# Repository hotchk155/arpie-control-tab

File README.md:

# arpie-control-tab

This project is a reference design for the 3 x potentiometer plus one momentary switch sidecar board for the ARPIE arpeggiator

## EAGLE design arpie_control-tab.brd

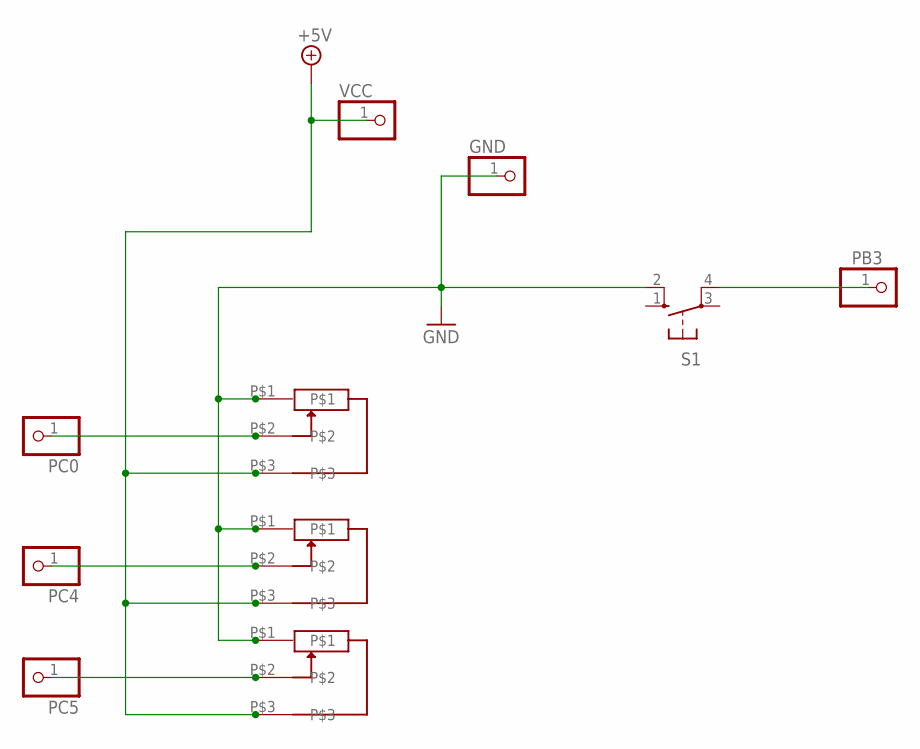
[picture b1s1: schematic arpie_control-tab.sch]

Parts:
GND: PINHD-1X1; 1X01
PB3: PINHD-1X1; 1X01
PC0, PC4, PC5: PINHD-1X1; 1X01
S1: 10-XX; B3F-10XX
U$1, U$2, U$3: PCBMOUNTPOT
VCC: PINHD-1X1; 1X01

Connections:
+5V: U$1.P$3, U$2.P$3, U$3.P$3, VCC.1
GND: GND.1, S1.2 (S1), U$1.P$1, U$2.P$1, U$3.P$1
unnamed: PB3.1, S1.4 (P1)
unnamed: PC0.1, U$1.P$2
unnamed: PC4.1, U$2.P$2
unnamed: PC5.1, U$3.P$2

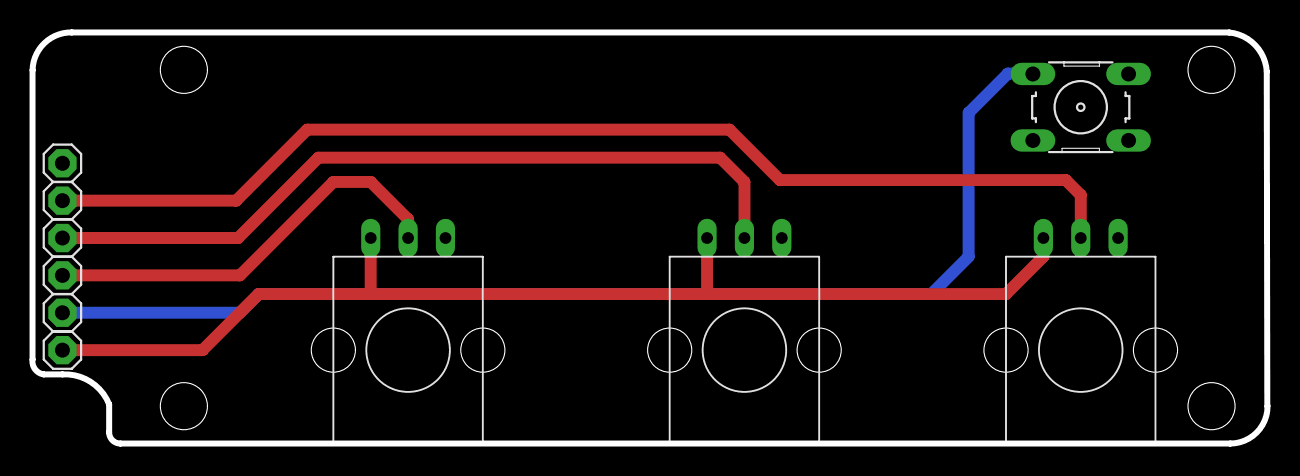
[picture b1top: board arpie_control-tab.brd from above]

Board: 2 copper layers, 84.0 x 27.9 mm, 10 parts (0 on the bottom side), 6 nets.

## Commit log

2014-12-01 :tada: Added .gitattributes & .gitignore files
2015-07-04 images
